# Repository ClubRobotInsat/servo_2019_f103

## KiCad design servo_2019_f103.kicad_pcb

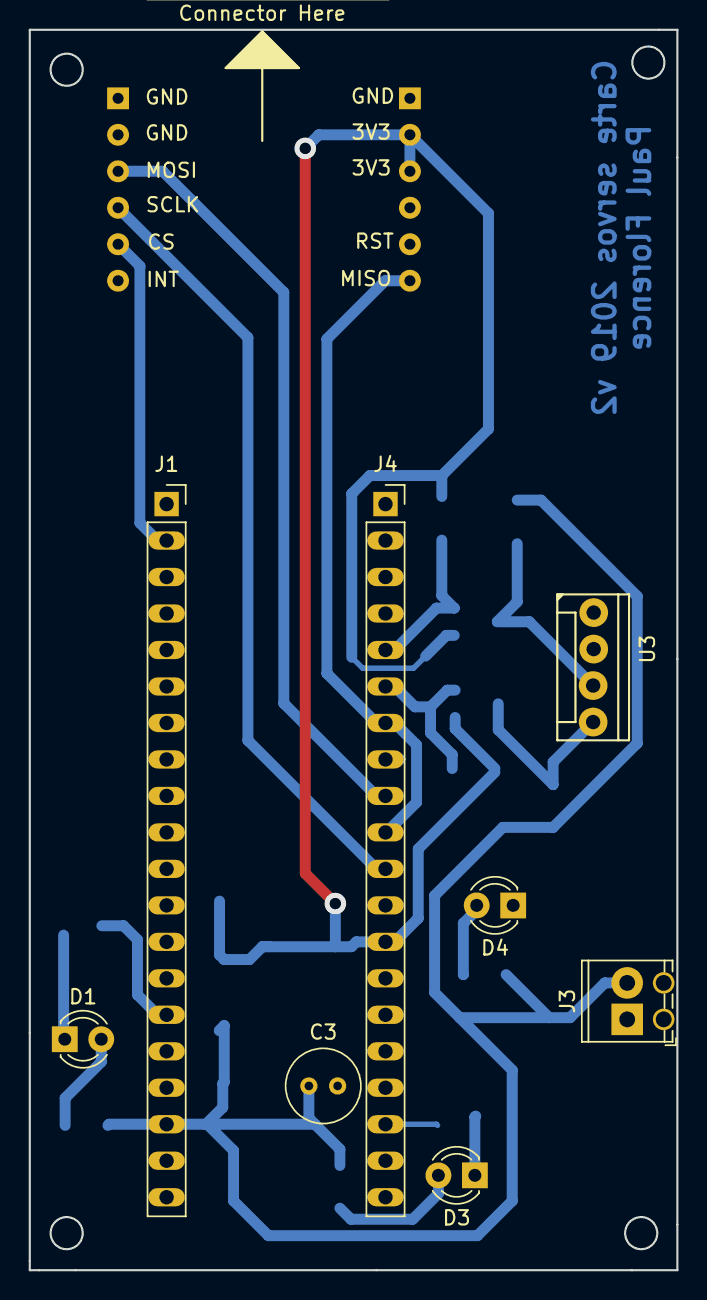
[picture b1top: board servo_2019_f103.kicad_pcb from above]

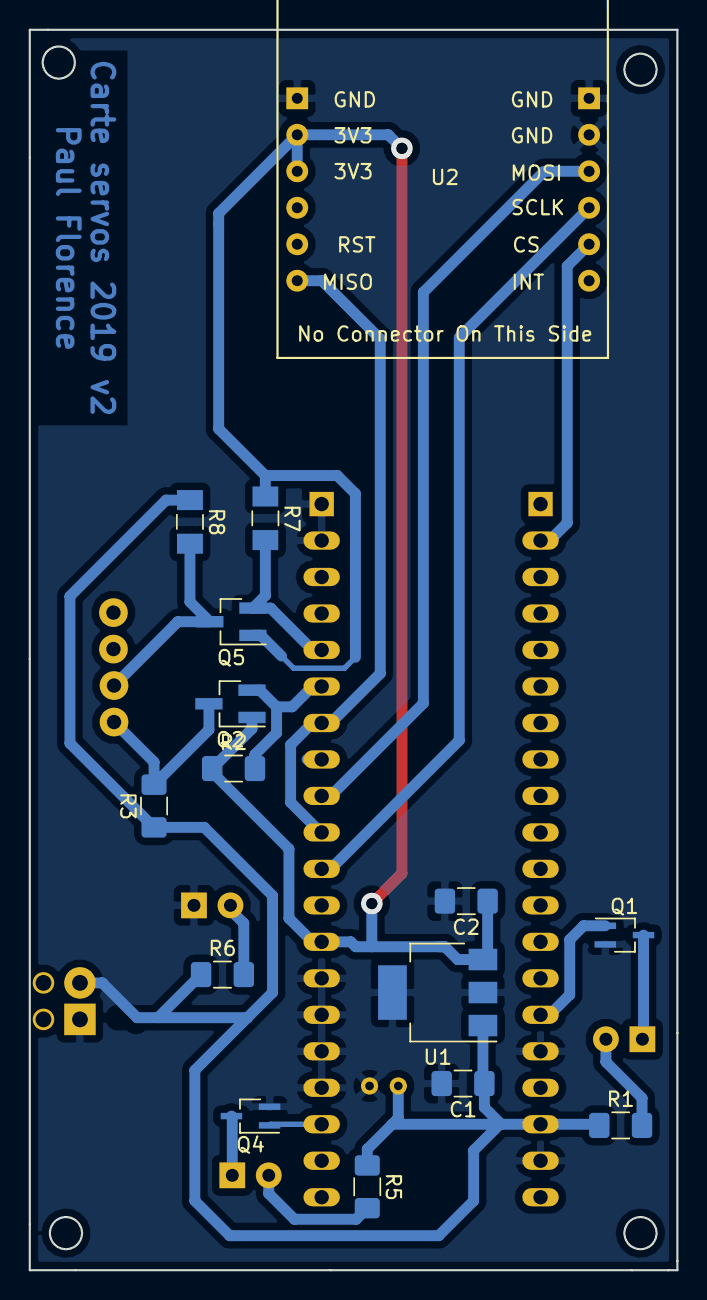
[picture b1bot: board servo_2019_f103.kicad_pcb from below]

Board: 2 copper layers, 45.1 x 86.4 mm, 23 parts (14 on the bottom side), 18 nets.

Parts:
C1, C2: 1u; C_1206_3216Metric_Pad1.42x1.75mm_HandSolder
C3: 100uF; C_Radial_D5.0mm_H7.0mm_P2.00mm
D1: LED_hardfault_jaune; LED_D3.0mm
D3: led_feedback_vert; LED_D3.0mm
D4: LED_alimentation_rouge; LED_D3.0mm
J1, J4: Conn_01x20_Female; PinSocket_1x20_P2.54mm_Vertical_Long_Pads
J3: Alim logique; TerminalBlock_Phoenix_MPT-0,5-2-2.54_1x02_P2.54mm_Horizontal
Q1, Q4: PMF370XN; SOT-323_SC-70_Handsoldering
Q2, Q5: BSS138; SOT-23_Handsoldering
R1, R5, R6: 150; R_1206_3216Metric_Pad1.42x1.75mm_HandSolder
R2, R3: 10kR; R_1206_3216Metric_Pad1.42x1.75mm_HandSolder
R7, R8: 10kR; R_1206_3216Metric_Pad1.39x1.80mm_HandSolder
U1: TC1262-33; SOT-223-3_TabPin2
U2: w5500
U3: servo_connector; HE14-4-straight

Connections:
+3V3: C2.1, J4.13, Q2.1, Q5.1, R2.1, R7.1, U1.3, U2.10, U2.11
+5V: C1.1, C3.1, J1.18, J3.2, R1.1, R3.1, R5.1, R6.1, R8.1, U1.1
/3.3V_logic_rx: J4.5, Q5.2, R7.2
/3.3V_logic_tx: J4.6, Q2.2, R2.2
/5V_logic_rx: Q5.3, R8.2, U3.3
/5V_logic_tx: Q2.3, R3.2, U3.4
/cs: J1.2, U2.2
/led_feedback: J4.18, Q4.1
/led_hardfault: J1.15, Q1.1
/miso: J4.7, J4.10, U2.7
/mosi: J4.9, U2.4
/sck: J4.11, U2.3
GND: C1.2, C2.2, C3.2, D4.1, J1.16, J1.19, J3.1, J4.1, J4.2, J4.14, J4.15, J4.16, J4.17, Q1.2, Q4.2, U1.2, U2.5, U2.6, U2.12
unnamed: D1.1, Q1.3
unnamed: D1.2, R1.2
unnamed: D3.1, Q4.3
unnamed: D3.2, R5.2
unnamed: D4.2, R6.2

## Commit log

2018-11-24 Schematic for the black-pill servomotor board.
2019-01-20 Import generic card template
2019-01-20 update first try at rooting
2019-01-21 changed the led packages and added missing routes
2019-01-21 added text to print the card without side mistakes
2019-01-21 saved the actual modifications on the schematic
2019-02-05 Fix wrong w5500 footprint
2019-05-08 Add version number and drill hole on PCB
2019-05-18 Unhide layers
2019-05-28 Use bss138 Update connectors Add decoupling capacitor
